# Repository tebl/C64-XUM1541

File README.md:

# C64 XUM1541

The thing about old 5 1/4 inch floppies is that no matter the way they are stored, they are inherently in a constant decay until they're all disolved into nostalgia and tears. Because of that I wanted to archive my private collection of less than original floppy disks (I didn't know any better and I had a hard time being able to even afford empty disks). Anyway, I came across an interesting [blog-post](https://myoldcomputer.nl/commodore-64/xum1541-promicro/) where a dedicated superfan used an Arduino Pro Micro to connect the drive directly to a modern computer, allowing a disk to be copied to a D64-file within a minute!

There are more professional solutions out there with a lot more features, but I wanted the simplest version of it all without actually soldering wires myself - so I threw together a simple PCB with the footprints matching parts I already had laying around in my parts-bin from building my Pi1541 module.

## Building the module
The module only consists of a handful of components, so just enure that get the components matching the BOM listed at the bottom of this page and solder it all together (component counts in parenthesis are not needed for a minimal build). The PCB may seem somewhat oversized for what it is, the reason for this is that I wanted it to fit into one of the 70x45x30mm electronic project boxes - when doing so you'd also install the power LED listed as an optional component, but bent out toward the side so that you can see it inside the box.

I you're building more than one of these, you probably won't need to install the reset switch on more than one of them (it is used when initially flashing the Arduino Pro Micro).

## Using the module
Using the actual module is a chapter unto itself, so I've put together a separate [firmware installation document](https://github.com/tebl/C64-XUM1541/blob/master/documentation/firmware.md) describing how to flash the Arduino Pro Micro with the correct firmware as well as set it up with the OpenCBM software for use on a Windows 10 computer. If you're on a different platform, you'll have to look up those guides separately as I only have the one laptop.

There is also an extensive document available that describes the various commands that can be used as part of the [OpenCBM](https://spiro.trikaliotis.net/opencbm#download)-package, this can be found within the install-folder on your computer. With everything working correctly, you're ready to start archiving and for those just wanting to start copying things the command you're looking for is probably the following:
```
d64copy.exe 8 disk.d64
```

**WARNING!** A quick note on the hardware itself is that there is a recommended way of unplugging and plugging in cables, mainly to never do so with the power supplied to it. Commodore 64s and their associated hardware is slowly going extinct like the disks we're trying to archive, so please handle them with the care they deserve!

# Schematic
The supplied KiCad files should be sufficient as both a schematic and as a  starting point for ordering PCBs (basically you could just zip the contents of the export folder and upload that on a fabrication site), the schematic is also available in [PDF-format](https://github.com/tebl/C64-XUM1541/raw/master/C64%20XUM1541/export/C64%20XUM1541.pdf) and this is what you'll need to print and work your way through this things don't work as expected after assembly.

# BOM
Most parts should be easy to get a hold of from your favourite local electronic component shop, but given that I don't have access to such shops where I live so everything was based on whatever I could get cheapest from ebay/AliExpress (free shipping, plan on usually waiting 3-4 weeks though). The list below should be everything you'll need in addition to a workable soldering iron and some 60/40 soldering tin.

Any part counts listed in parenthesis are optional, meaning you can skip installing those features if it is a feature you don't want/need. Male pin headers are usually supplied in breakable 40-pin packages, so you'll just use what you need and discard the rest. Installing female pin headers may be preferable as it makes it easier to recover the Arduino Pro Micro for later projects.

| Reference    | Item                                  | Count |
| ------------ | ------------------------------------- | ----- |
| PCB          | Fabricate using Gerber files ([order](https://www.pcbway.com/project/shareproject/Commodore_64_XUM1541.html?inviteid=88707))          |     1 |
| A1           | Arduino Pro Micro *                    |     1 |
| A1           | 12-pin headers                         |     2 |
| A1           | 12-pin female pin headers              |   (2) |
| D1           | 5mm LED                                |   (1) |    
| J1           | Female S-terminal 6pin DIN PCB         |     1 |
| J2           | 2x8 male pin headers                   |   (1) |
| R1           | 330 ohm resistor                       |   (1) | 
|              | 70x45x30mm electronic project box      |   (1) |
| SW1          | 6x6x5mm right-angle momentary button   |     1 |

*) I've purchased a couple of different Arduino Pro Micro boards that had a different physical size, so take care to match up the pins to the PCB so that you solder it up to match the board you own.

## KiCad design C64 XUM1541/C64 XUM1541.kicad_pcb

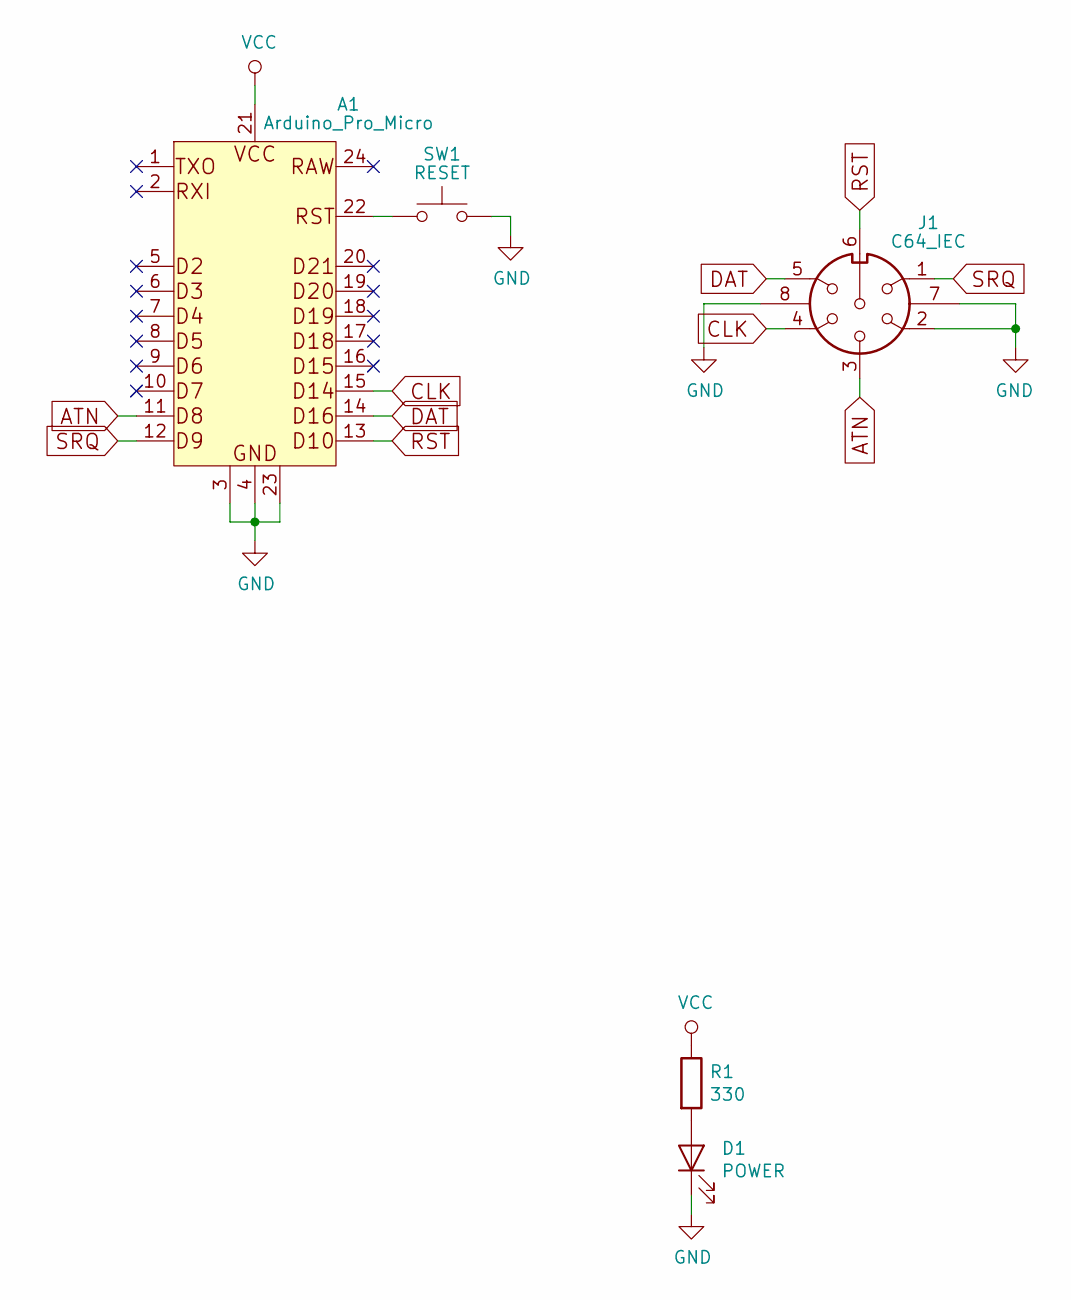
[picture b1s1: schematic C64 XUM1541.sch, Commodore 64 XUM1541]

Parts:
A1: Arduino_Pro_Micro
D1: POWER; LED_D5.0mm
J1: C64_IEC
R1: 330; R_Axial_DIN0207_L6.3mm_D2.5mm_P10.16mm_Horizontal
SW1: RESET; SW_Tactile_SPST_Angled_PTS645Vx39-2LFS

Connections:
ATN: A1.11 (D8), J1.3
CLK: A1.15 (D14), J1.4
DAT: A1.14 (D16), J1.5
GND: A1.3 (GND), A1.4 (GND), A1.23 (GND), D1.1 (K), J1.2, J1.7, J1.8, SW1.2
unnamed: A1.22 (RST), SW1.1
unnamed: D1.2 (A), R1.2
RST: A1.13 (D10), J1.6
SRQ: A1.12 (D9), J1.1
VCC: A1.21 (VCC), R1.1

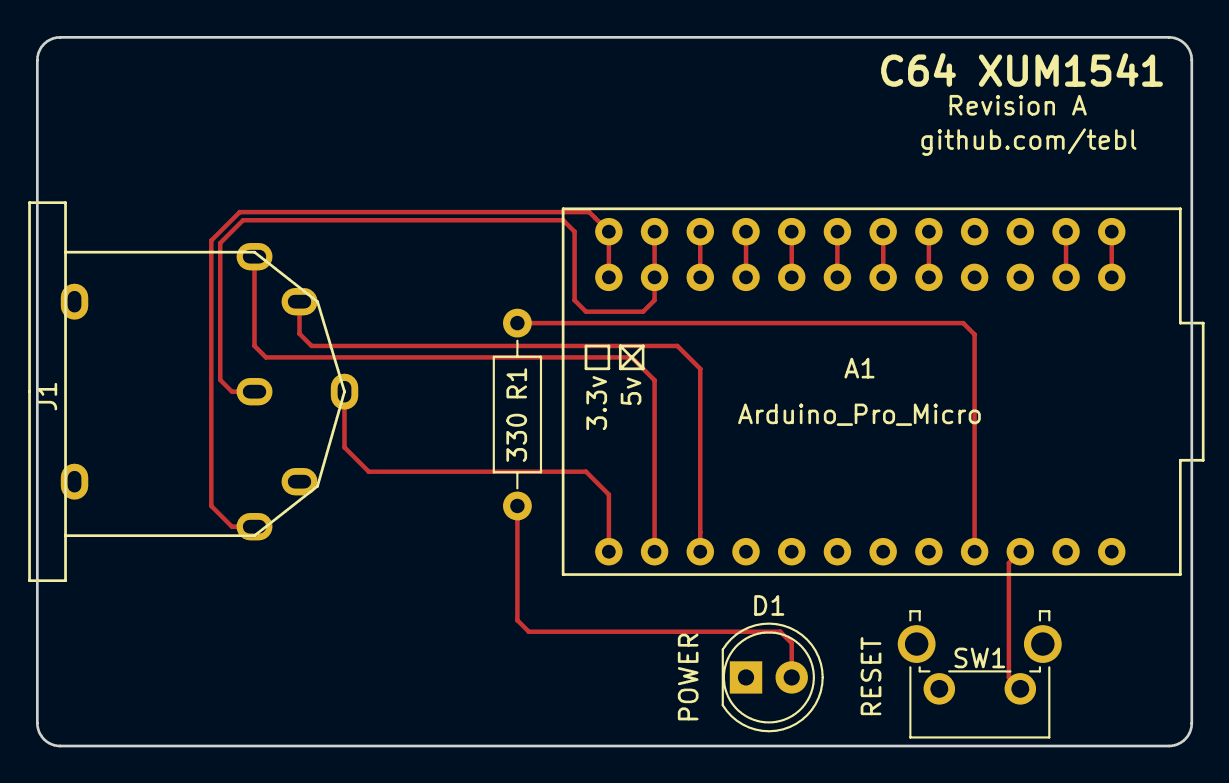
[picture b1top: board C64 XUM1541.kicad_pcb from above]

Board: 2 copper layers, 64.1 x 39.4 mm, 5 parts (0 on the bottom side), 9 nets.

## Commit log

2020-06-07 Bare PCB
2020-06-08 Basic module
2020-06-20 Usage notes
2020-06-20 Gallery images
2020-06-21 Added README
2020-06-22 Added parallel header
2020-06-22 Updated link
2020-06-22 Update link to schematic
